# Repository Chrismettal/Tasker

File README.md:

Reworked version of Reminder with Google Calendar providing the same functionality as the original design, but providing an etched PCB making the build much cleaner and easier while providing a bit more documentation.
The PCB mostly uses SMD parts and includes everything to enable USB-upload just like a Wemos D1 mini for example.

Please check out Andreas' video of his original design:
https://www.youtube.com/watch?v=sm1-l5-z3ag

Based on the original analog version to use 5 Buttons and 5 LEDs with available GPIO.

A PCF8574 port expander is routed over i2c on the PCB but currently not implemented in source code. Does not need to be placed for the rest to function. Could be implemented for further external triggers to set/reset automated functions.

# Buying

The PCB is now stocked on my Tindie store!

**If you like my work please consider [supporting my caffeine addiction](https://github.com/Chrismettal#donations)!**

# Build Notes

Upload the gerber files made to your favourite PCB shop (or write me, i have spares).
The micro usb footprint is the "Wuerth Micro-B #629105150521" type, but a lot of chinese noname ones fit. If you can't get "the real thing" just look for a pack of various sizes. Some will fit.
__Flux it up!__
Start by placing the usb jack first as the CH340G will block your access a bit should you mess up the fine pins of the jack. Then place all the resistors, capacitos, transistors, then the bigger ICs and the crystal.
Only after all SMD parts are placed put in the buttons.

__Double check LED, C6 and C9 polarity!__

- C6 and C9 are tantalum caps that explode violently when you get their polarity wrong. The stripe (positive) should point to the C6/C9 writing on the PCB.
- R22 and R23 are optional I2C pullups, should you use something like an LCD over the I2C bus.
- Should you plan to upload code to the ESP before placing it, you could leave out U1, Q1, Q2, C1, C2, R1, R2, R3, R4, Y1.
- It does not matter if you power the device via USB or directly wire in 5 V to the pin header.
- U4 is optional. Should you place it you also have to place R22 and R23 and set an adress via B0, B1, B2.
- P0 - P7 are the in/outputs of U4.
- That cheap, chinese Arduino clone in your drawer is a good source for the CH340G that you forgot to order.
- You could also just order the bigger version of a NodeMCU and steal the ESP, AMS1117-3.3 ,CH340G and S8050s from that if you own a hot air rework station.
- If you are unhappy with the brightness of the LEDs you could change the values of R15 - R19. 

# Case

The case is 3d printed just like the master, but a lot thinner and i hope more elegant. Any material is fine, no supports needed if you lay the top flat face down.
I use course M2*8 screws to mount the PCB in the upper part as well as screwing the upper part to the lower part, which gets mounted to a wall first.
Like the master you can just put stickers on the case next to the buttons or emboss your tasks into the top part STL.

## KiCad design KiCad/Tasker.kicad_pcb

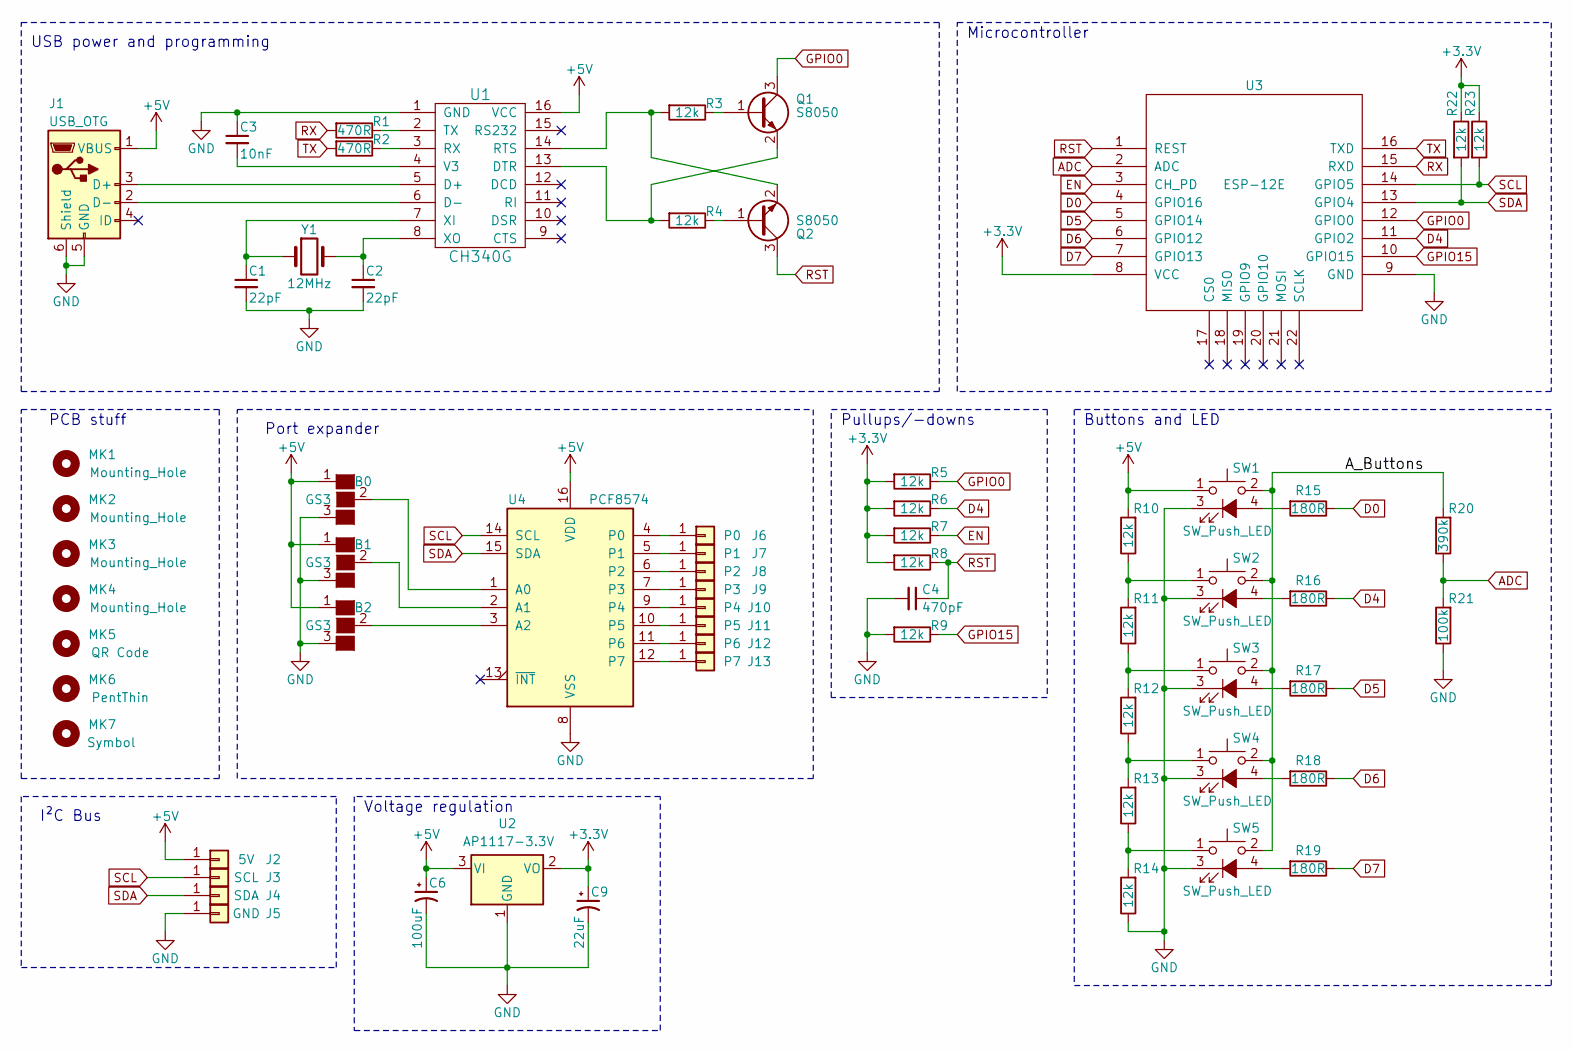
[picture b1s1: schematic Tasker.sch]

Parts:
B0, B1, B2: GS3
C1, C2: 22pF; C_0805_HandSoldering
C3: 10nF; C_0805_HandSoldering
C4: 470pF; C_0805_HandSoldering
C6: 100uF; CP_Tantalum_Case-B_EIA-3528-21_Hand
C9: 22uF; CP_Tantalum_Case-B_EIA-3528-21_Hand
J1: USB_OTG; USB_Micro-B_Wuerth-629105150521
J2: 5V; Socket_Strip_Straight_1x01_Pitch2.54mm
J3: SCL; Socket_Strip_Straight_1x01_Pitch2.54mm
J4: SDA; Socket_Strip_Straight_1x01_Pitch2.54mm
J5: GND; Socket_Strip_Straight_1x01_Pitch2.54mm
J6: P0; Socket_Strip_Straight_1x01_Pitch2.54mm
J7: P1; Socket_Strip_Straight_1x01_Pitch2.54mm
J8: P2; Socket_Strip_Straight_1x01_Pitch2.54mm
J9: P3; Socket_Strip_Straight_1x01_Pitch2.54mm
J10: P4; Socket_Strip_Straight_1x01_Pitch2.54mm
J11: P5; Socket_Strip_Straight_1x01_Pitch2.54mm
J12: P6; Socket_Strip_Straight_1x01_Pitch2.54mm
J13: P7; Socket_Strip_Straight_1x01_Pitch2.54mm
MK1, MK2, MK3, MK4: Mounting_Hole; EigenesMountingHole_2.7mm_M2.5
MK5: QR Code; QR_Tasker
MK6: PentThin
MK7: Symbol; Dickbutt
Q1, Q2: S8050; SOT-23_Handsoldering
R1, R2: 470R; R_0805_HandSoldering
R3, R4, R5, R6, R7, R8, R9, R10, R11, R12, R13, R14, R22, R23: 12k; R_0805_HandSoldering
R15, R16, R17, R18, R19: 180R; R_0805_HandSoldering
R20: 390k; R_0805_HandSoldering
R21: 100k; R_0805_HandSoldering
SW1, SW2, SW3, SW4, SW5: SW_Push_LED; 12mm_LED_pushbutton
U1: CH340G; SOIC-16_3.9x9.9mm_Pitch1.27mm
U2: AP1117-3.3V; SOT-223-3_TabPin2
U3: ESP-12E; ESP-12E_SMD
U4: PCF8574; SOIC-16W_7.5x10.3mm_Pitch1.27mm
Y1: 12MHz; Crystal_SMD_HC49-SD_HandSoldering

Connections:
+3V3: C9.1, R5.2, R6.2, R7.2, R8.2, R22.1, R23.1, U2.2 (VO), U3.8 (VCC)
+5V: B0.1 (G1), B1.1 (G1), B2.1 (G1), C6.1, J1.1 (VBUS), J2.1, R10.2, SW1.1, U1.16 (VCC), U2.3 (VI), U4.16 (VDD)
/A_Buttons: R20.2, SW1.2, SW2.2, SW3.2, SW4.2, SW5.2
ADC: R20.1, R21.2, U3.2 (ADC)
D0: R15.1, U3.4 (GPIO16)
D4: R6.1, R16.1, U3.11 (GPIO2)
D5: R17.1, U3.5 (GPIO14)
D6: R18.1, U3.6 (GPIO12)
D7: R19.1, U3.7 (GPIO13)
EN: R7.1, U3.3 (CH_PD)
GND: B0.3 (G3), B1.3 (G3), B2.3 (G3), C1.2, C2.2, C3.1, C4.2, C6.2, C9.2, J1.5 (GND), J1.6 (Shield), J5.1, R9.2, R14.1, R21.1, SW1.3 (K), SW2.3 (K), SW3.3 (K), SW4.3 (K), SW5.3 (K), U1.1 (GND), U2.1 (GND), U3.9 (GND), U4.8 (VSS)
GPIO0: Q1.3 (C), R5.1, U3.12 (GPIO0)
GPIO15: R9.1, U3.10 (GPIO15)
unnamed: B0.2 (G2), U4.1 (A0)
unnamed: B1.2 (G2), U4.2 (A1)
unnamed: B2.2 (G2), U4.3 (A2)
unnamed: C1.1, U1.7 (XI), Y1.1
unnamed: C2.1, U1.8 (XO), Y1.2
unnamed: C3.2, U1.4 (V3)
unnamed: J1.2 (D-), U1.6 (D-)
unnamed: J1.3 (D+), U1.5 (D+)
unnamed: J6.1, U4.4 (P0)
unnamed: J7.1, U4.5 (P1)
unnamed: J8.1, U4.6 (P2)
unnamed: J9.1, U4.7 (P3)
unnamed: J10.1, U4.9 (P4)
unnamed: J11.1, U4.10 (P5)
unnamed: J12.1, U4.11 (P6)
unnamed: J13.1, U4.12 (P7)
unnamed: Q1.1 (B), R3.1
unnamed: Q1.2 (E), R4.2, U1.13 (DTR)
unnamed: Q2.1 (B), R4.1
unnamed: Q2.2 (E), R3.2, U1.14 (RTS)
unnamed: R1.1, U1.2 (TX)
unnamed: R2.1, U1.3 (RX)
unnamed: R10.1, R11.2, SW2.1
unnamed: R11.1, R12.2, SW3.1
unnamed: R12.1, R13.2, SW4.1
unnamed: R13.1, R14.2, SW5.1
unnamed: R15.2, SW1.4 (A)
unnamed: R16.2, SW2.4 (A)
unnamed: R17.2, SW3.4 (A)
unnamed: R18.2, SW4.4 (A)
unnamed: R19.2, SW5.4 (A)
RST: C4.1, Q2.3 (C), R8.1, U3.1 (REST)
RX: R1.2, U3.15 (RXD)
SCL: J3.1, R23.2, U3.14 (GPIO5), U4.14 (SCL)
SDA: J4.1, R22.2, U3.13 (GPIO4), U4.15 (SDA)
TX: R2.2, U3.16 (TXD)

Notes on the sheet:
USB power and programming
Pullups/-downs
Voltage regulation
Microcontroller
Buttons and LED
PCB stuff
I²C Bus
Port expander

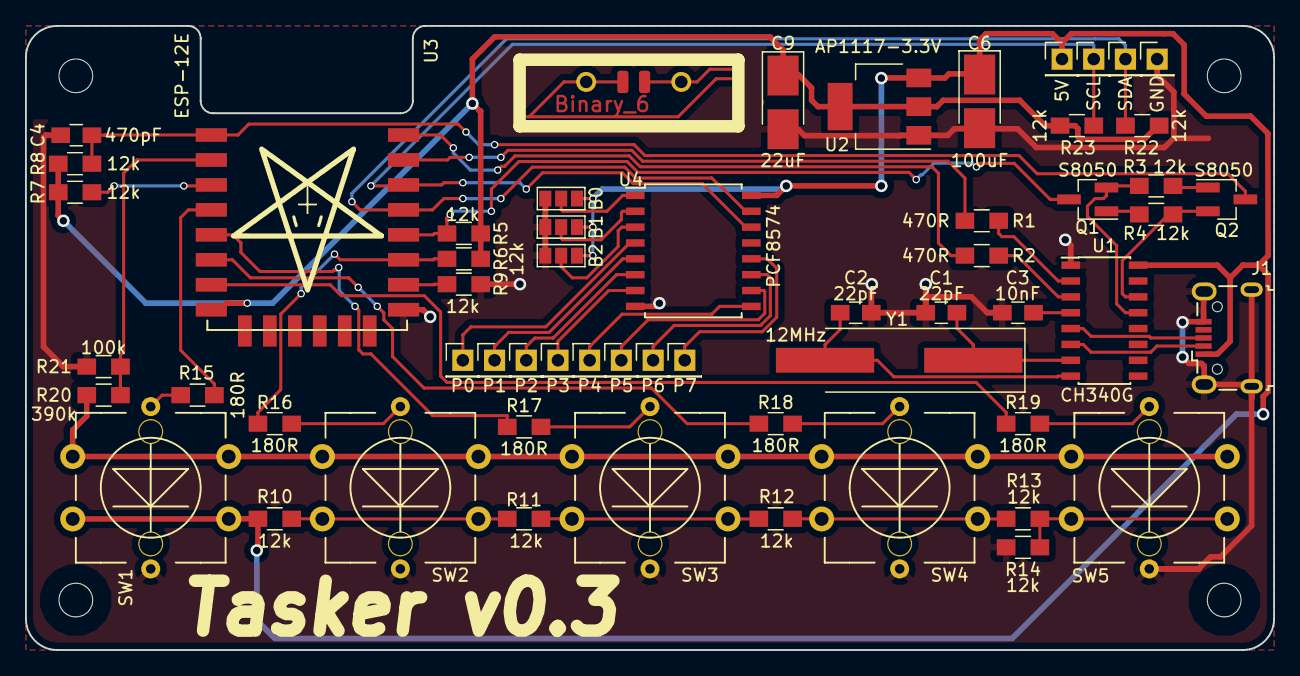
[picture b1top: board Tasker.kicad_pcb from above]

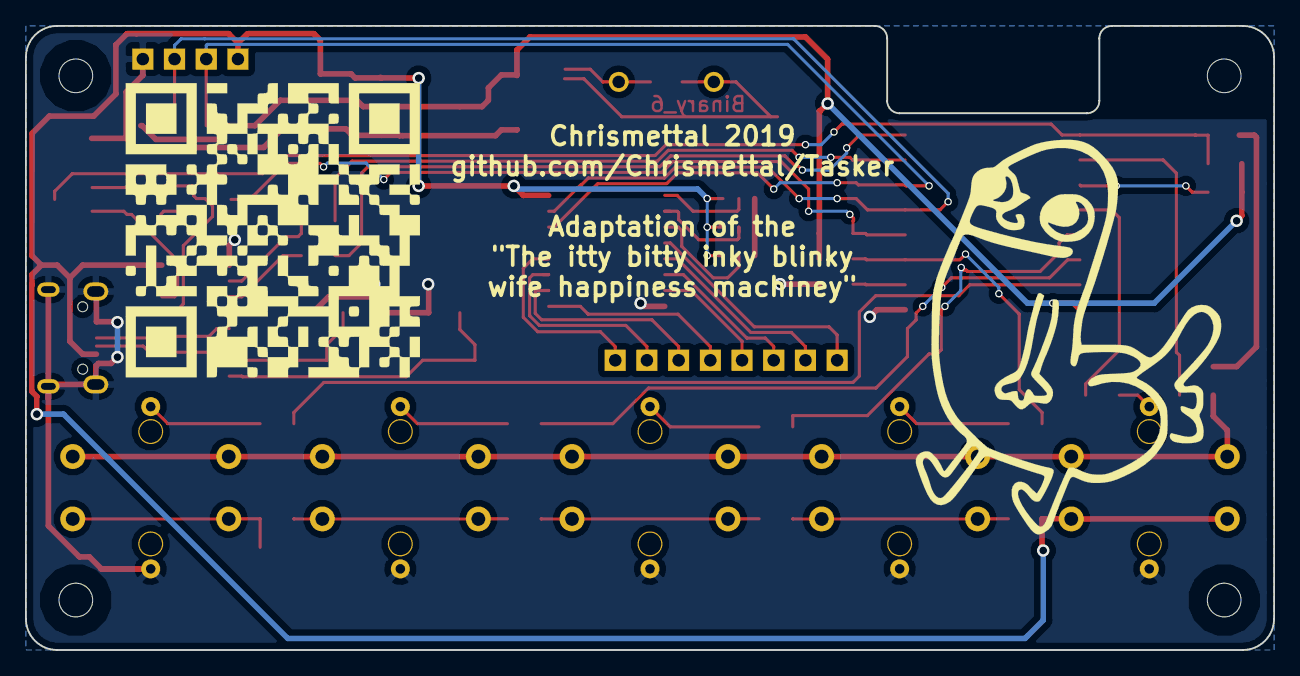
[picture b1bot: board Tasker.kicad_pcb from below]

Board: 2 copper layers, 100.0 x 50.0 mm, 65 parts (2 on the bottom side), 49 nets.

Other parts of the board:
H7: Symbol_Binary6; Binary_6_v0.1

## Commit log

2019-06-04 Initial upload of remixed project
2021-05-27 Update readme with store information
2021-07-10 MOVING TO GITLAB
2021-08-21 Fix image links
2023-05-01 Remove Kofi
